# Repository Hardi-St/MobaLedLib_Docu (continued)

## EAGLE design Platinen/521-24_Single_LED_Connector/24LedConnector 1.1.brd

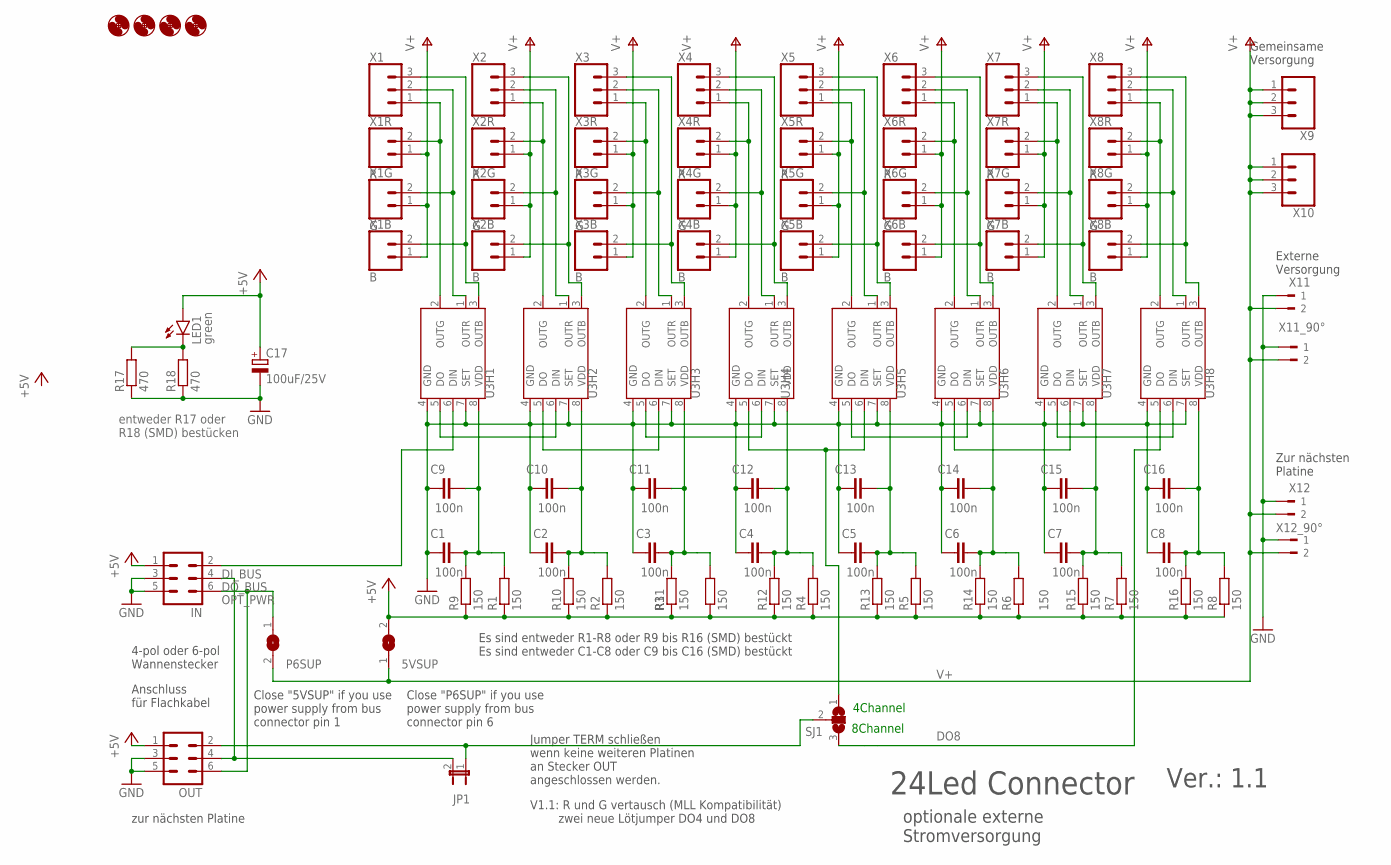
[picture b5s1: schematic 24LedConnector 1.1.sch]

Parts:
5VSUP: SJ
C1, C2, C3, C4, C5, C6, C7, C8: 100n; C025-024X044
C9, C10, C11, C12, C13, C14, C15, C16: 100n; C0805
C17: 100uF/25V; E3,5-8
H1, H2, H3, H4: MOUNT-HOLE2.0; 2,0
IN: ML6
JP1: JP1E; JP1
LED1: green; LED3MM
OUT: ML6
P6SUP: SJ
R1, R2, R3, R4, R5, R6, R7, R8: 150; 0204V
R9, R10, R11, R12, R13, R14, R15, R16: 150; M0805
R17: 470; M0805
R18: 470; 0204V
SJ1: SJ2W; SJ_2
U3H1, U3H2, U3H3, U3H4, U3H5, U3H6, U3H7, U3H8: WS2811; SOP8
X1, X2, X3, X4, X5, X6, X7, X8, X9, X10: CONN_03SCREW-NS; SCREWTERMINAL-3.5MM-3-NS
X1B, X2B, X3B, X4B, X5B, X6B, X7B, X8B: B; 1X02
X1G, X2G, X3G, X4G, X5G, X6G, X7G, X8G: G; 1X02
X1R, X2R, X3R, X4R, X5R, X6R, X7R, X8R: R; 1X02
X11, X12: 180-2
X11_90°, X12_90°: 90-2

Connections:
+5V: 5VSUP.2, C17.+, IN.1, LED1.A, OUT.1, R1.1, R2.1, R3.1, R4.1, R5.1, R6.1, R7.1, R8.1, R9.1, R10.1, R11.1, R12.1, R13.1, R14.1, R15.1, R16.1
B1: U3H1.3 (OUTB), X1.3, X1B.2
B2: U3H2.3 (OUTB), X2.3, X2B.2
B3: U3H3.3 (OUTB), X3.3, X3B.2
B4: U3H4.3 (OUTB), X4.3, X4B.2
B5: U3H5.3 (OUTB), X5.3, X5B.2
B6: U3H6.3 (OUTB), X6.3, X6B.2
B7: U3H7.3 (OUTB), X7.3, X7B.2
B8: U3H8.3 (OUTB), X8.3, X8B.2
DI_BUS: IN.2, U3H1.6 (DIN)
DO1DI2: U3H1.5 (DO), U3H2.6 (DIN)
DO2DI3: U3H2.5 (DO), U3H3.6 (DIN)
DO3DI4: U3H3.5 (DO), U3H4.6 (DIN)
DO4DI5: SJ1.1, U3H4.5 (DO), U3H5.6 (DIN)
DO5DI6: U3H5.5 (DO), U3H6.6 (DIN)
DO6DI7: U3H6.5 (DO), U3H7.6 (DIN)
DO7DI8: U3H7.5 (DO), U3H8.6 (DIN)
DO8: SJ1.3, U3H8.5 (DO)
DO_BUS: IN.4, JP1.2, OUT.4
DO_MODULE: JP1.1, OUT.2, SJ1.2
G1: U3H1.1 (OUTR), X1.2, X1G.2
G2: U3H2.1 (OUTR), X2.2, X2G.2
G3: U3H3.1 (OUTR), X3.2, X3G.2
G4: U3H4.1 (OUTR), X4.2, X4G.2
G5: U3H5.1 (OUTR), X5.2, X5G.2
G6: U3H6.1 (OUTR), X6.2, X6G.2
G7: U3H7.1 (OUTR), X7.2, X7G.2
G8: U3H8.1 (OUTR), X8.2, X8G.2
GND: C1.1, C2.1, C3.1, C4.1, C5.1, C6.1, C7.1, C8.1, C9.1, C10.1, C11.1, C12.1, C13.1, C14.1, C15.1, C16.1, C17.-, IN.3, IN.5, OUT.3, OUT.5, R17.1, R18.1, U3H1.4 (GND), U3H1.7 (SET), U3H2.4 (GND), U3H2.7 (SET), U3H3.4 (GND), U3H3.7 (SET), U3H4.4 (GND), U3H4.7 (SET), U3H5.4 (GND), U3H5.7 (SET), U3H6.4 (GND), U3H6.7 (SET), U3H7.4 (GND), U3H7.7 (SET), U3H8.4 (GND), U3H8.7 (SET), X11.1, X11_90°.1, X12.1, X12_90°.1
OPT_PWR: IN.6, OUT.6, P6SUP.1
POWERLED: LED1.K (C), R17.2, R18.2
R1: U3H1.2 (OUTG), X1.1, X1R.2
R2: U3H2.2 (OUTG), X2.1, X2R.2
R3: U3H3.2 (OUTG), X3.1, X3R.2
R4: U3H4.2 (OUTG), X4.1, X4R.2
R5: U3H5.2 (OUTG), X5.1, X5R.2
R6: U3H6.2 (OUTG), X6.1, X6R.2
R7: U3H7.2 (OUTG), X7.1, X7R.2
R8: U3H8.2 (OUTG), X8.1, X8R.2
V+: 5VSUP.1, P6SUP.2, X1B.1, X1G.1, X1R.1, X2B.1, X2G.1, X2R.1, X3B.1, X3G.1, X3R.1, X4B.1, X4G.1, X4R.1, X5B.1, X5G.1, X5R.1, X6B.1, X6G.1, X6R.1, X7B.1, X7G.1, X7R.1, X8B.1, X8G.1, X8R.1, X9.1, X9.2, X9.3, X10.1, X10.2, X10.3, X11.2, X11_90°.2, X12.2, X12_90°.2
VDD'1: C1.2, C9.2, R1.2, R9.2, U3H1.8 (VDD)
VDD'2: C2.2, C10.2, R2.2, R10.2, U3H2.8 (VDD)
VDD'3: C3.2, C11.2, R3.2, R11.2, U3H3.8 (VDD)
VDD'4: C4.2, C12.2, R4.2, R12.2, U3H4.8 (VDD)
VDD'5: C5.2, C13.2, R5.2, R13.2, U3H5.8 (VDD)
VDD'6: C6.2, C14.2, R6.2, R14.2, U3H6.8 (VDD)
VDD'7: C7.2, C15.2, R7.2, R15.2, U3H7.8 (VDD)
VDD'8: C8.2, C16.2, R8.2, R16.2, U3H8.8 (VDD)

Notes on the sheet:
Anschluss für Flachkabel
4-pol oder 6-pol Wannenstecker
Close "P6SUP" if you use power supply from bus connector pin 6
zur nächsten Platine
Gemeinsame Versorgung
24Led Connector
optionale externe Stromversorgung
Ver.: 1.1
Jumper TERM schließen wenn keine weiteren Platinen an Stecker OUT angeschlossen werden.
Zur nächsten Platine
Close "5VSUP" if you use power supply from bus connector pin 1
Externe Versorgung
Es sind entweder R1-R8 oder R9 bis R16 (SMD) bestückt Es sind entweder C1-C8 oder C9 bis C16 (SMD) bestückt
entweder R17 oder R18 (SMD) bestücken
V1.1: R und G vertausch (MLL Kompatibilität) zwei neue Lötjumper DO4 und DO8
4Channel
8Channel

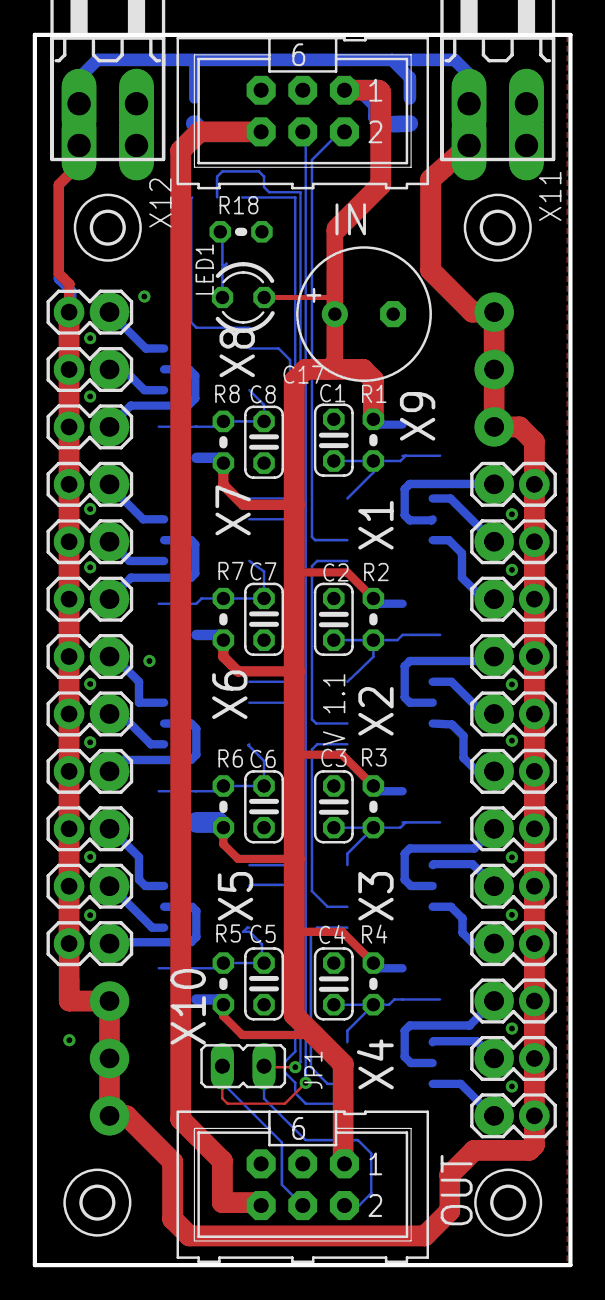
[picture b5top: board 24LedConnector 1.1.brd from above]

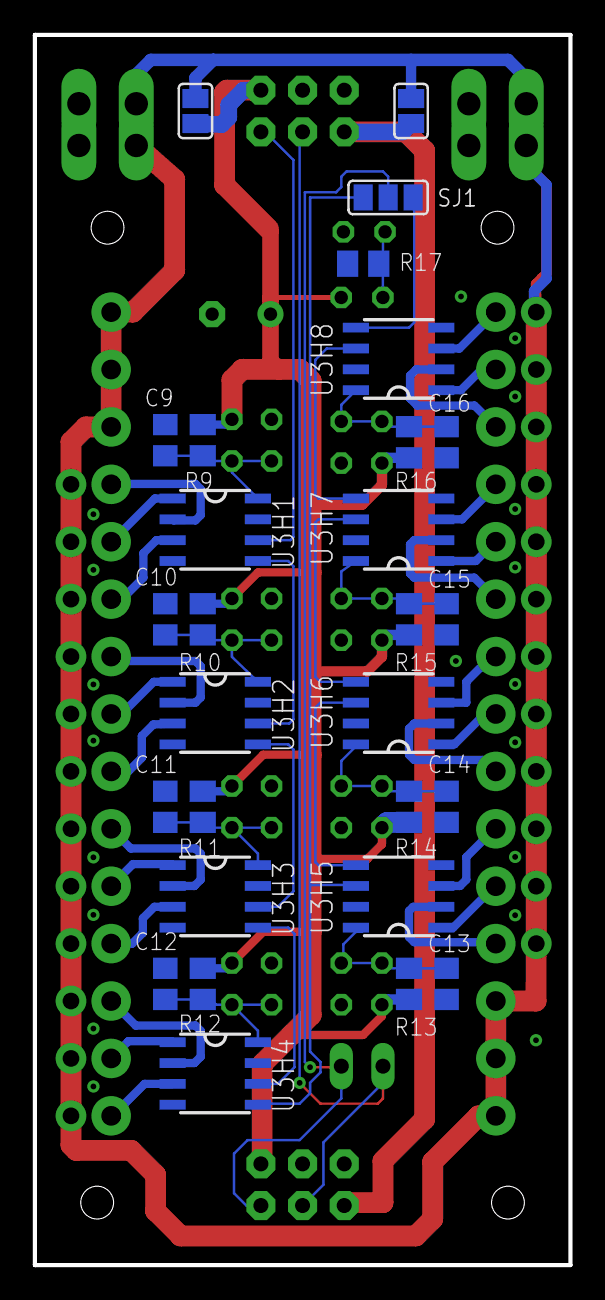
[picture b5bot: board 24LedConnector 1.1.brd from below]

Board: 2 copper layers, 32.7 x 75.0 mm, 92 parts (28 on the bottom side), 48 nets.

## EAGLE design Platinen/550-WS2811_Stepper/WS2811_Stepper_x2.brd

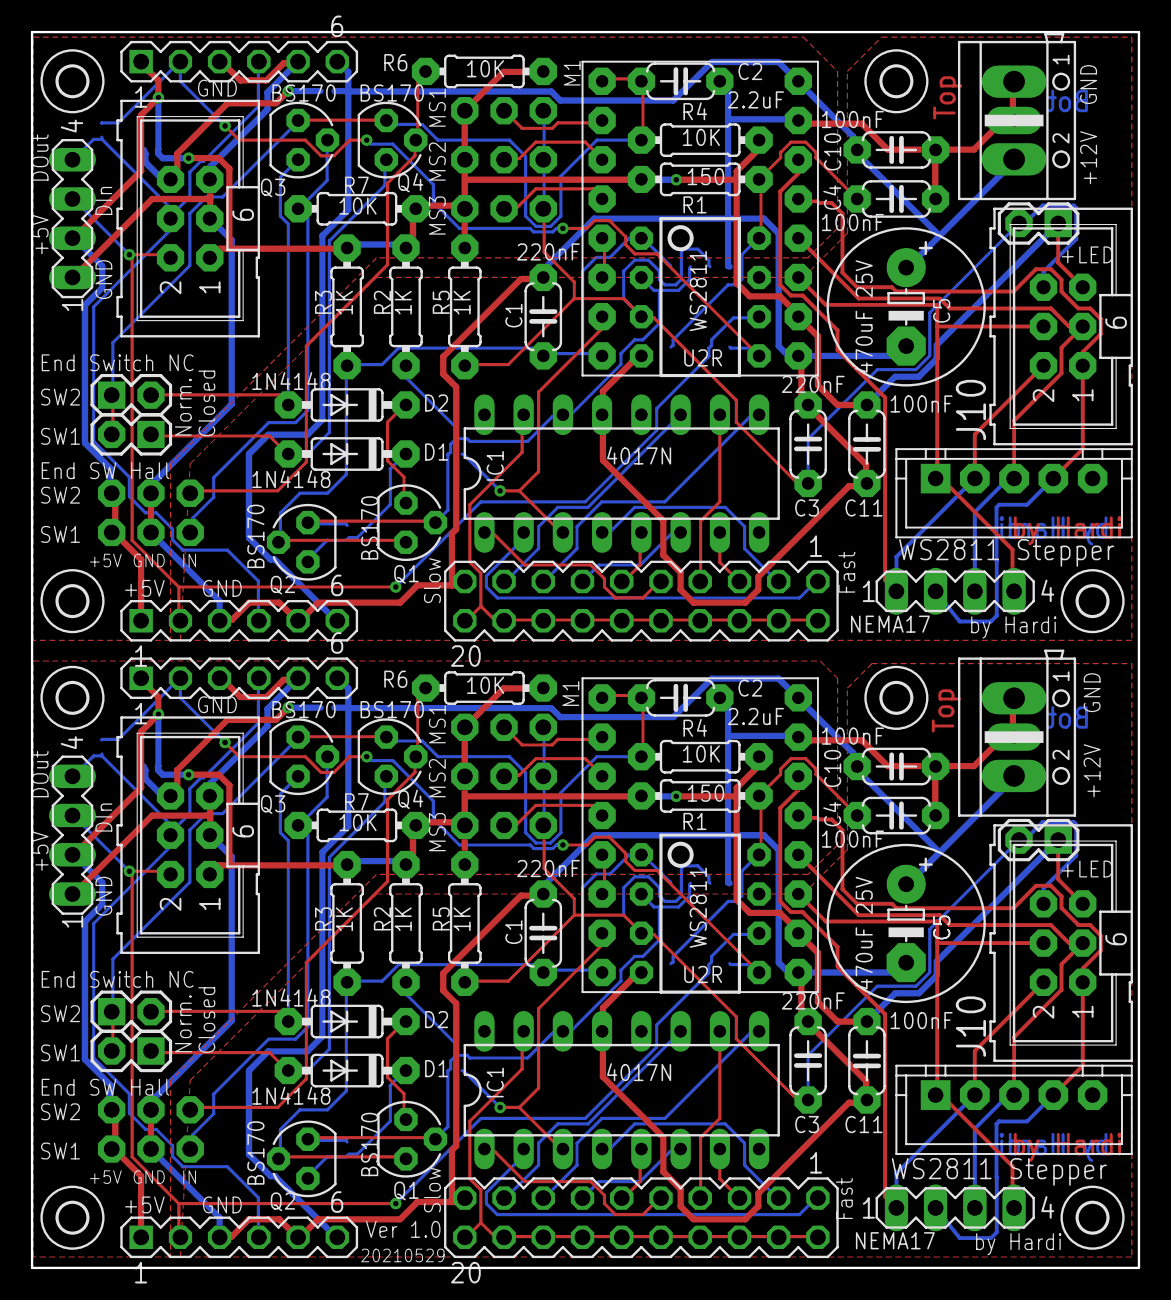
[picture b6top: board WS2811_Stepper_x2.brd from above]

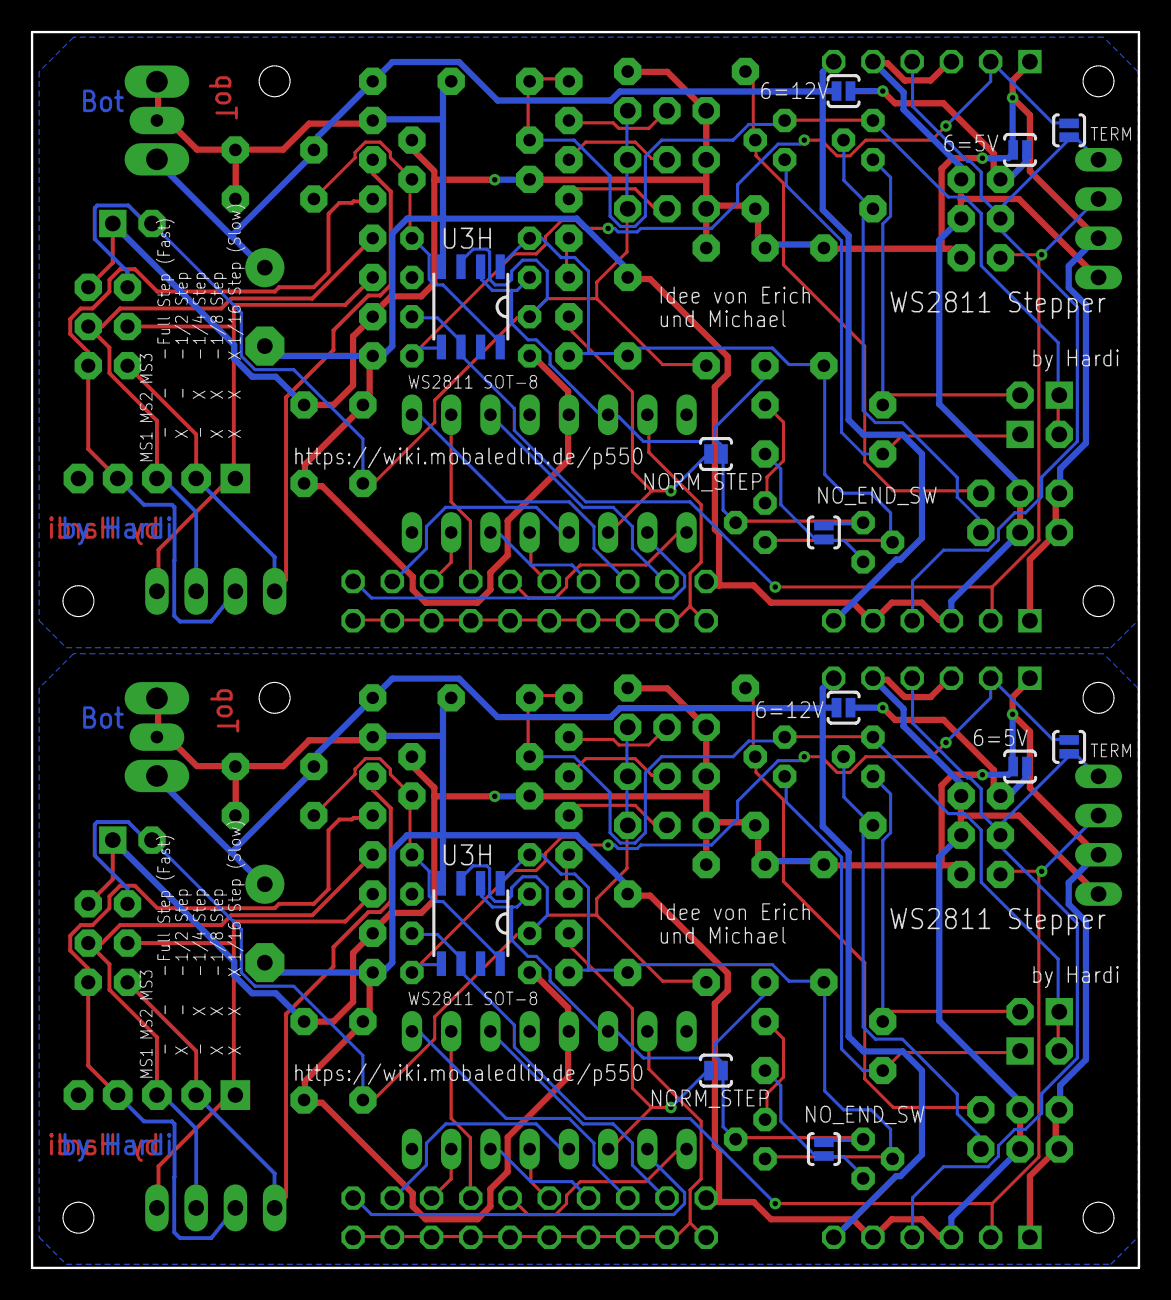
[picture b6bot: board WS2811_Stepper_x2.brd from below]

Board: 2 copper layers, 71.7 x 80.0 mm, 100 parts (12 on the bottom side), 74 nets.

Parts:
6=5V, 6=5V1, 6=12V, 6=12V1: SOLDERJUMPERNO; SJ_2S-NO
C1, C3, C6, C12: 220nF; C050-024X044
C2, C9: 2.2uF; C050-024X044
C4, C7, C8, C10, C11, C14: 100nF; C050-024X044
C5, C13: 470uF 25V; E5-10,5
CON1, CON8: End SW1; 1X02
CON2, CON9: End SW2; 1X02
CON3, CON11: End SW1H; 1X03-CLEANBIG
CON4, CON10: STEPPER_CON
CON5, CON12: End SW2H; 1X03-CLEANBIG
CON6, CON13: NEMA17; MA04-1
CON7, CON14: LED; 1X02
D1, D2, D3, D4: 1N4148; DO35-7
H1, H2, H3, H4, H5, H6, H7, H8: MOUNT-HOLE2.0; 2,0
IC1, IC2: 4017N; DIL16
IN, IN1: ML6
J1, J10: ML6
JP1, JP4: MS1; 1X03-CLEANBIG
JP2, JP5: MS2; 1X03-CLEANBIG
JP3, JP6: MS3; 1X03-CLEANBIG
M1, M2: BOARD_A4988
NORM_STEP, NORM_STEP1: SOLDERJUMPERNO; SJ_2S-NO
NO_END_SW, NO_END_SW1: SOLDERJUMPERNO; SJ_2S-NO
Q1, Q2, Q3, Q4, Q5, Q6, Q7, Q8: BS170; SOT54E
R1, R8: 150; RCL_0204/7
R2, R3, R5, R9, R10, R12: 1K; RCL_0204/7
R4, R6, R7, R11, R13, R14: 10K; RCL_0204/7
SV1, SV3, SV5, SV6: MA06-1
SV2, SV7: MA04-1
SV4, SV8: MA10-2
TERM, TERM1: SOLDERJUMPERNO; SJ_2S-NO
U2R, U2R1: WS2811; S3PO_MODUL_WS2811_SOUND_MP3-TF-16P_WS2811_AND_ATTINY_WS2811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
U3H, U3H1: WS2811 SOT-8; SOP8
X1, X2: AK500/2+M

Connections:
+5V: 6=5V.2, C11.1, CON3.1, CON5.1, CON7.1, IN.1, J10.5, JP1.1, JP2.1, JP3.1, M1.+5V, R1.1, R2.2, R3.2, R4.2, R5.2, R6.2, R7.2, SV1.1, SV2.2, SV3.1
+5V1: 6=5V1.2, C8.1, CON11.1, CON12.1, CON14.1, IN1.1, J1.5, JP4.1, JP5.1, JP6.1, M2.+5V, R8.1, R9.2, R10.2, R11.2, R12.2, R13.2, R14.2, SV5.1, SV6.1, SV7.2
DIR: C1.1, M1.DIR, Q1.S, Q2.G, R3.1, U2R.1, U3H.1
DIR1: C6.1, M2.DIR, Q5.S, Q6.G, R10.1, U2R1.1, U3H1.1
GND: C1.2, C2.2, C3.2, C4.2, C5.-, C10.2, C11.2, CON3.2, CON5.2, IC1.13, IN.3, IN.5, M1.GND, M1.GNDMOT, SV1.3, SV1.5, SV2.1, SV3.3, SV3.5, SV4.19, U2R.4, U3H.4, X1.1, X1.M
GND1: C6.2, C7.2, C8.2, C9.2, C12.2, C13.-, C14.2, CON11.2, CON12.2, IC2.13, IN1.3, IN1.5, M2.GND, M2.GNDMOT, SV5.3, SV5.5, SV6.3, SV6.5, SV7.1, SV8.19, U2R1.4, U3H1.4, X2.1, X2.M
LED: C3.1, CON7.2, J10.6, JP1.3, JP2.3, JP3.3, R5.1, U2R.3, U3H.3
LED1: C12.1, CON14.2, J1.6, JP4.3, JP5.3, JP6.3, R12.1, U2R1.3, U3H1.3
unnamed: M1.RESET, M1.SLEEP
unnamed: IN.2, SV1.2, SV2.3, U2R.6, U3H.6
unnamed: SV3.2, TERM.2, U2R.5, U3H.5
unnamed: IN.4, SV1.4, SV2.4, SV3.4, TERM.1
unnamed: C4.1, R1.2, U2R.8, U3H.8
unnamed: C2.1, CON1.1, CON2.2, M1.ENABLE, Q3.D, Q4.D, R4.1
unnamed: 6=12V.1, C5.+, C10.1, M1.VMOT, SV1.6, SV3.6, X1.2
unnamed: CON2.1, D1.A, Q4.S
unnamed: CON1.2, D2.A, Q3.S
unnamed: CON5.3, Q4.G, R6.1
unnamed: D2.C, Q1.D
unnamed: JP6.2, M2.MS3
unnamed: D1.C, NO_END_SW.1, Q2.D
unnamed: JP2.2, M1.MS2
unnamed: 6=5V.1, 6=12V.2, IN.6
unnamed: CON3.3, Q3.G, R7.1
unnamed: JP5.2, M2.MS2
unnamed: IC1.2, SV4.1
unnamed: IC1.4, SV4.3
unnamed: IC1.7, SV4.5
unnamed: IC1.10, SV4.7
unnamed: JP1.2, M1.MS1
unnamed: IC1.1, SV4.9
unnamed: IC1.5, SV4.11
unnamed: IC1.6, SV4.13
unnamed: IC1.9, SV4.15
unnamed: JP3.2, M1.MS3
unnamed: IC1.11, SV4.17
unnamed: IC1.15, SV4.2, SV4.4, SV4.6, SV4.8, SV4.10, SV4.12, SV4.14, SV4.16, SV4.18, SV4.20
unnamed: JP4.2, M2.MS1
unnamed: CON4.2, CON6.1, J10.2, M1.M2AB
unnamed: CON10.2, CON13.1, J1.2, M2.M2AB
unnamed: IC1.3, M1.STEP, NORM_STEP.2
unnamed: CON10.4, CON13.2, J1.1, M2.M2A
unnamed: CON4.1, CON6.4, J10.4, M1.M1B
unnamed: CON10.3, CON13.3, J1.3, M2.M1A
unnamed: CON10.1, CON13.4, J1.4, M2.M1B
unnamed: M2.RESET, M2.SLEEP
unnamed: IN1.2, SV5.2, SV7.3, U2R1.6, U3H1.6
unnamed: CON4.4, CON6.2, J10.1, M1.M2A
unnamed: CON4.3, CON6.3, J10.3, M1.M1A
unnamed: SV6.2, TERM1.2, U2R1.5, U3H1.5
unnamed: IN1.4, SV5.4, SV6.4, SV7.4, TERM1.1
unnamed: C14.1, R8.2, U2R1.8, U3H1.8
unnamed: 6=12V1.1, C7.1, C13.+, M2.VMOT, SV5.6, SV6.6, X2.2
unnamed: C9.1, CON8.1, CON9.2, M2.ENABLE, Q7.D, Q8.D, R11.1
unnamed: CON9.1, D3.A, Q8.S
unnamed: CON8.2, D4.A, Q7.S
unnamed: D4.C, Q5.D
unnamed: D3.C, NO_END_SW1.1, Q6.D
unnamed: CON11.3, Q7.G, R14.1
unnamed: CON12.3, Q8.G, R13.1
unnamed: IC2.4, SV8.3
unnamed: IC2.7, SV8.5
unnamed: IC2.10, SV8.7
unnamed: IC2.1, SV8.9
unnamed: IC2.5, SV8.11
unnamed: IC2.6, SV8.13
unnamed: IC2.9, SV8.15
unnamed: IC2.11, SV8.17
unnamed: IC2.15, SV8.2, SV8.4, SV8.6, SV8.8, SV8.10, SV8.12, SV8.14, SV8.16, SV8.18, SV8.20
unnamed: IC2.3, M2.STEP, NORM_STEP1.2
unnamed: IC2.2, SV8.1
unnamed: 6=5V1.1, 6=12V1.2, IN1.6
STEP: IC1.14, NORM_STEP.1, NO_END_SW.2, Q1.G, Q2.S, R2.1, U2R.2, U3H.2
STEP1: IC2.14, NORM_STEP1.1, NO_END_SW1.2, Q5.G, Q6.S, R9.1, U2R1.2, U3H1.2

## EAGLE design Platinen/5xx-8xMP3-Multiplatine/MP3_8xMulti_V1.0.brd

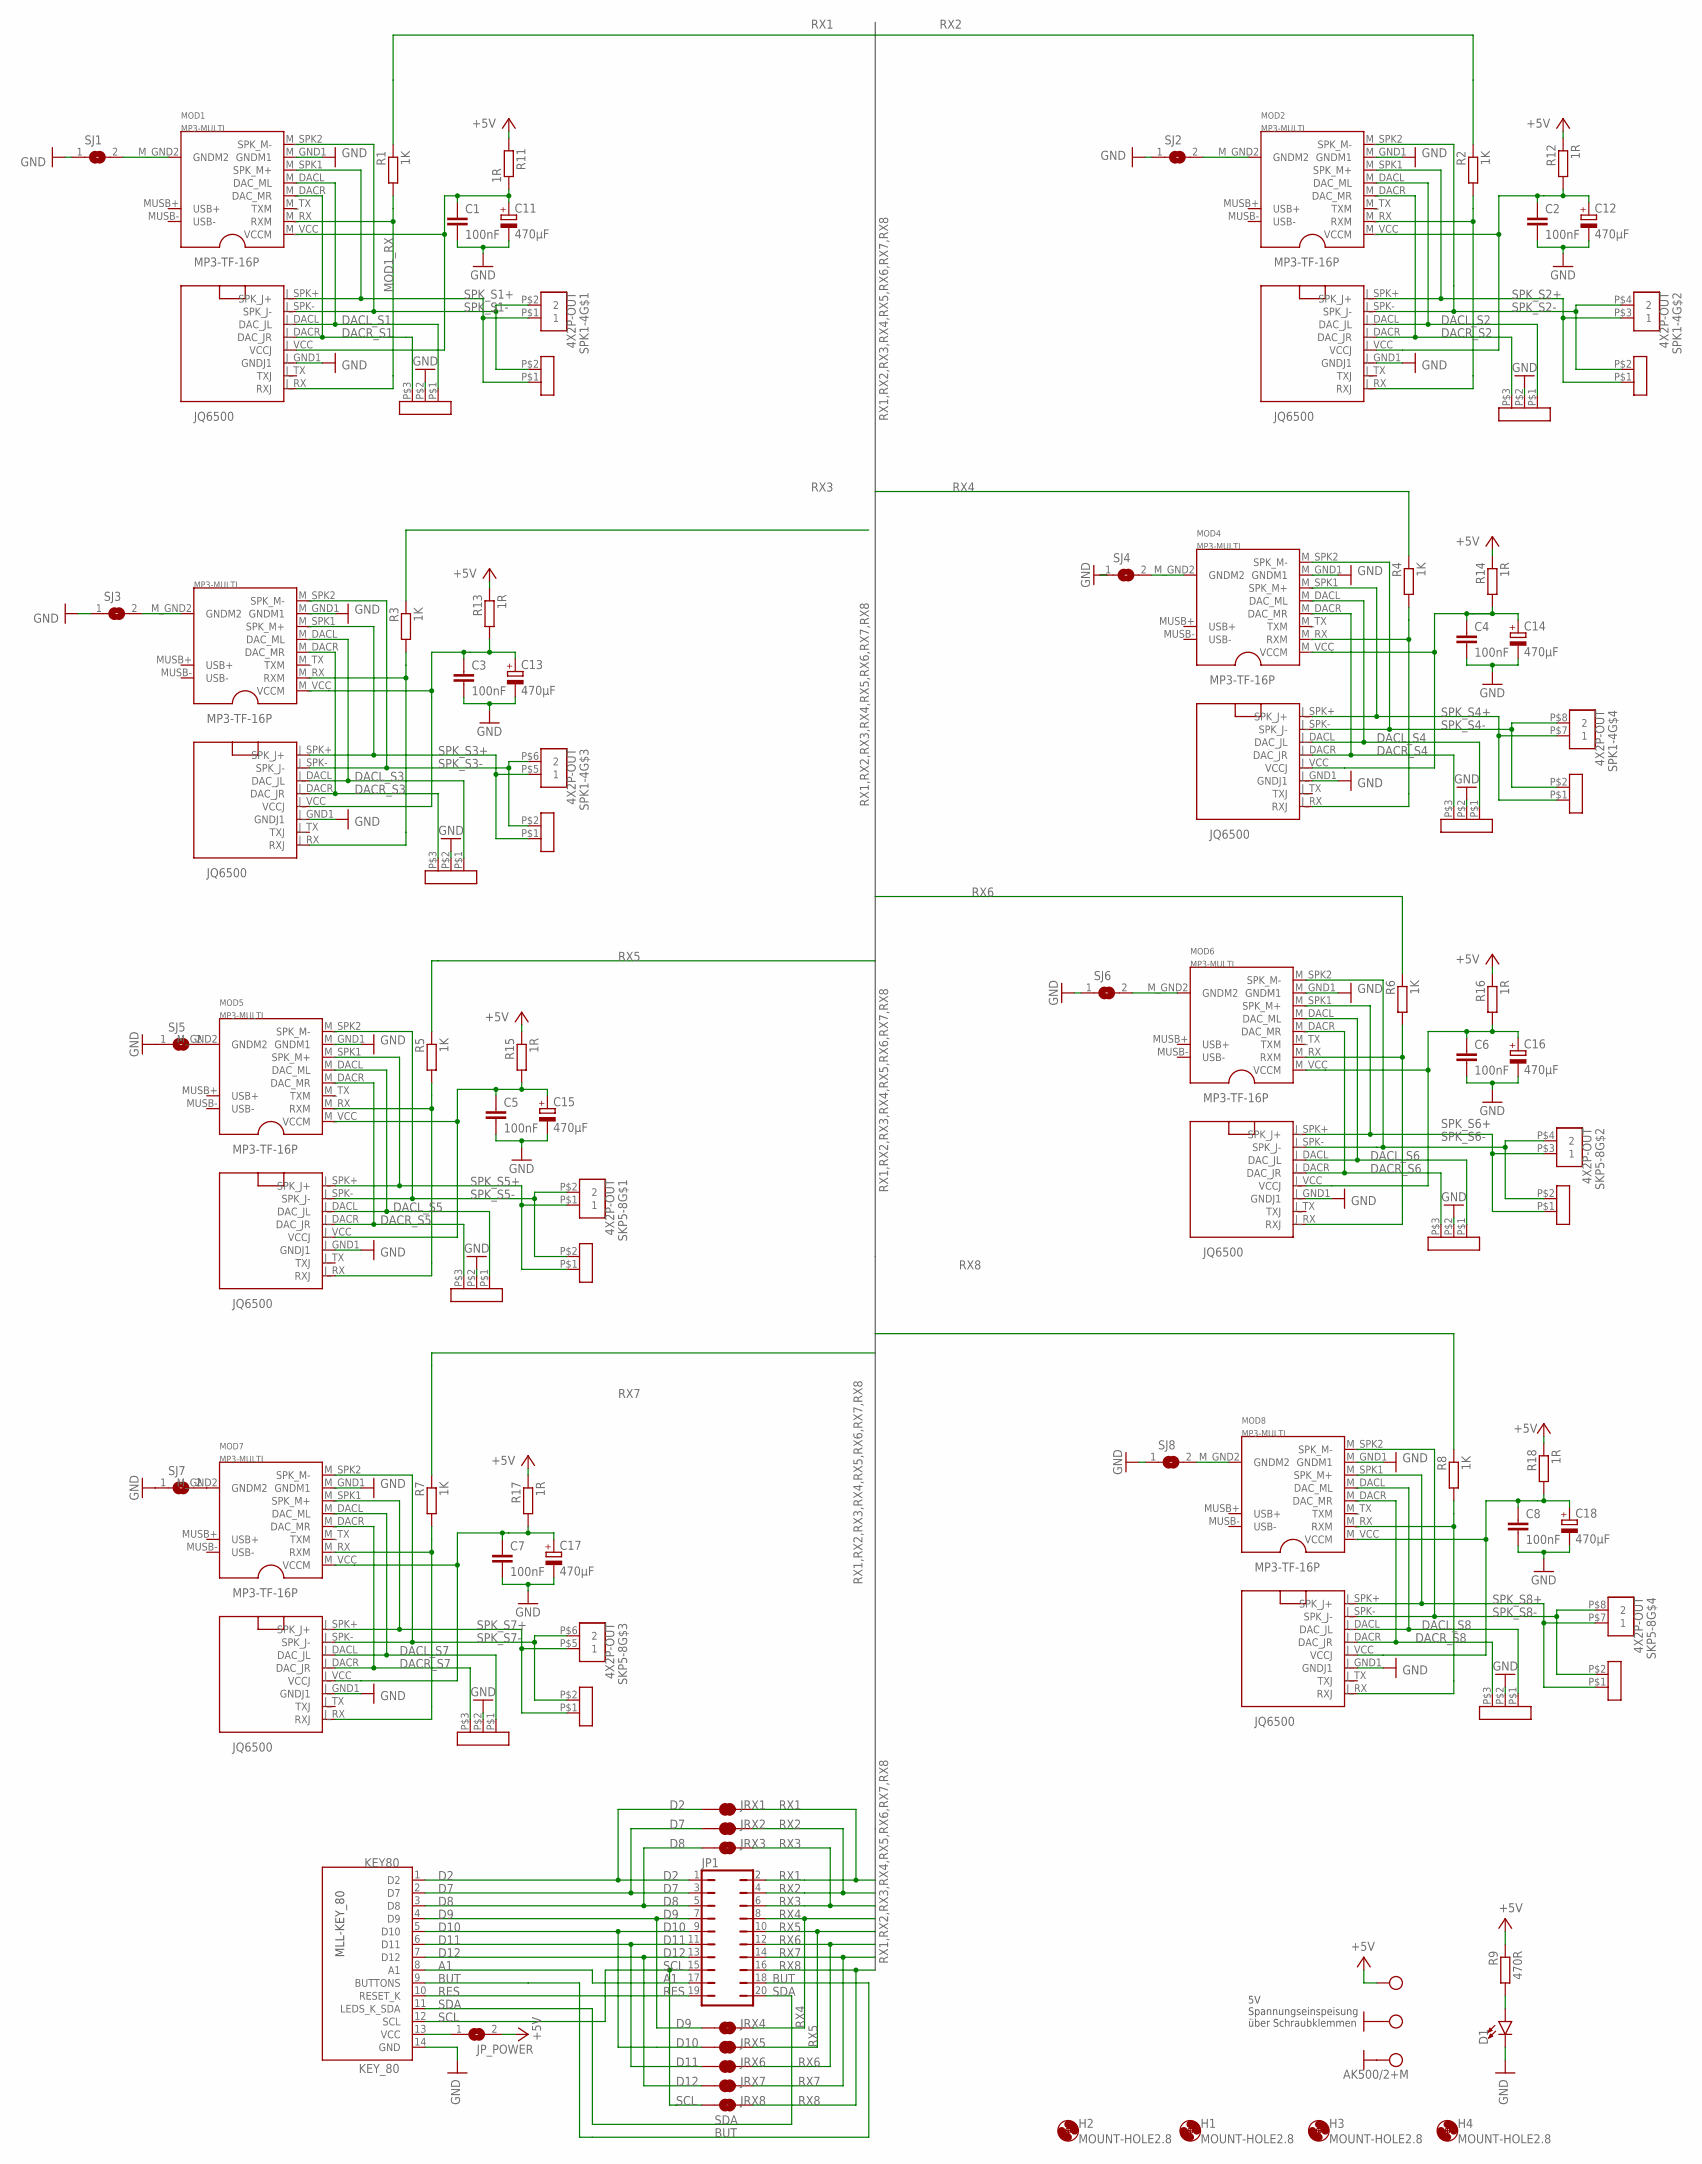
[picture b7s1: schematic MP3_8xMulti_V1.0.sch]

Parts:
C1, C2, C3, C4, C5, C6, C7, C8: 100nF; C025-025X050
C11, C12, C13, C14, C15, C16, C17, C18: 470µF; E5-8,5
D1: LED3MM; LED_3MM
DAC1, DAC2, DAC3, DAC4, DAC5, DAC6, DAC7, DAC8: 3XRM254
H1, H2, H3, H4: MOUNT-HOLE2.8; 2,8
JP1: JP10Q
JP_POWER: SJ
JRX1, JRX2, JRX3, JRX4, JRX5, JRX6, JRX7, JRX8: JUMPER-SMT_2_NC_TRACE_NO-SILK; SMT-JUMPER_2_NC_TRACE_NO-SILK
KEY80: KEY_80; IDC14
MOD1, MOD2, MOD3, MOD4, MOD5, MOD6, MOD7, MOD8: MP3-MULTI; MP3-TF16P_JQ6500
R1, R2, R3, R4, R5, R6, R7, R8: 1K; 0207/7
R9: 470R; 0207/7
R11, R12, R13, R14, R15, R16, R17, R18: 1R; 0207/7
SJ1, SJ2, SJ3, SJ4, SJ5, SJ6, SJ7, SJ8: SJ
SKP5-8: 4X2P-OUT; DG308
SPK1, SPK2, SPK3, SPK4, SPK5, SPK6, SPK7, SPK8: 2XRM254
SPK1-4: 4X2P-OUT; DG308
X1: AK500/2+M

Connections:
+5V: JP_POWER.2, R9.1, R11.2, R12.1, R13.1, R14.1, R15.1, R16.1, R17.1, R18.1, X1.2
A1: JP1.17, KEY80.8 (A1)
BUT: JP1.18, KEY80.9 (BUTTONS)
D2: JP1.1, JRX1.1, KEY80.1 (D2)
D7: JP1.3, JRX2.1, KEY80.2 (D7)
D8: JP1.5, JRX3.1, KEY80.3 (D8)
D9: JP1.7, JRX4.1, KEY80.4 (D9)
D10: JP1.9, JRX5.1, KEY80.5 (D10)
D11: JP1.11, JRX6.1, KEY80.6 (D11)
D12: JP1.13, JRX7.1, KEY80.7 (D12)
DACL_S1: DAC1.P$1, MOD1.J_DACL (DAC_JL), MOD1.M_DACL (DAC_ML)
DACL_S2: DAC2.P$1, MOD2.J_DACL (DAC_JL), MOD2.M_DACL (DAC_ML)
DACL_S3: DAC3.P$1, MOD3.J_DACL (DAC_JL), MOD3.M_DACL (DAC_ML)
DACL_S4: DAC4.P$1, MOD4.J_DACL (DAC_JL), MOD4.M_DACL (DAC_ML)
DACL_S5: DAC5.P$1, MOD5.J_DACL (DAC_JL), MOD5.M_DACL (DAC_ML)
DACL_S6: DAC6.P$1, MOD6.J_DACL (DAC_JL), MOD6.M_DACL (DAC_ML)
DACL_S7: DAC7.P$1, MOD7.J_DACL (DAC_JL), MOD7.M_DACL (DAC_ML)
DACL_S8: DAC8.P$1, MOD8.J_DACL (DAC_JL), MOD8.M_DACL (DAC_ML)
DACR_S1: DAC1.P$3, MOD1.J_DACR (DAC_JR), MOD1.M_DACR (DAC_MR)
DACR_S2: DAC2.P$3, MOD2.J_DACR (DAC_JR), MOD2.M_DACR (DAC_MR)
DACR_S3: DAC3.P$3, MOD3.J_DACR (DAC_JR), MOD3.M_DACR (DAC_MR)
DACR_S4: DAC4.P$3, MOD4.J_DACR (DAC_JR), MOD4.M_DACR (DAC_MR)
DACR_S5: DAC5.P$3, MOD5.J_DACR (DAC_JR), MOD5.M_DACR (DAC_MR)
DACR_S6: DAC6.P$3, MOD6.J_DACR (DAC_JR), MOD6.M_DACR (DAC_MR)
DACR_S7: DAC7.P$3, MOD7.J_DACR (DAC_JR), MOD7.M_DACR (DAC_MR)
DACR_S8: DAC8.P$3, MOD8.J_DACR (DAC_JR), MOD8.M_DACR (DAC_MR)
GND: C1.2, C2.2, C3.2, C4.2, C5.2, C6.2, C7.2, C8.2, C11.-, C12.-, C13.-, C14.-, C15.-, C16.-, C17.-, C18.-, D1.K (C), DAC1.P$2, DAC2.P$2, DAC3.P$2, DAC4.P$2, DAC5.P$2, DAC6.P$2, DAC7.P$2, DAC8.P$2, KEY80.14 (GND), MOD1.J_GND1 (GNDJ1), MOD1.M_GND1 (GNDM1), MOD2.J_GND1 (GNDJ1), MOD2.M_GND1 (GNDM1), MOD3.J_GND1 (GNDJ1), MOD3.M_GND1 (GNDM1), MOD4.J_GND1 (GNDJ1), MOD4.M_GND1 (GNDM1), MOD5.J_GND1 (GNDJ1), MOD5.M_GND1 (GNDM1), MOD6.J_GND1 (GNDJ1), MOD6.M_GND1 (GNDM1), MOD7.J_GND1 (GNDJ1), MOD7.M_GND1 (GNDM1), MOD8.J_GND1 (GNDJ1), MOD8.M_GND1 (GNDM1), SJ1.1, SJ2.1, SJ3.1, SJ4.1, SJ5.1, SJ6.1, SJ7.1, SJ8.1, X1.1, X1.M
LED1: D1.A, R9.2
MOD1_RX: MOD1.J_RX (RXJ), MOD1.M_RX (RXM), R1.2
MOD1_RX1: MOD2.J_RX (RXJ), MOD2.M_RX (RXM), R2.2
MOD1_RX2: MOD3.J_RX (RXJ), MOD3.M_RX (RXM), R3.2
MOD1_RX3: MOD4.J_RX (RXJ), MOD4.M_RX (RXM), R4.2
MOD1_RX4: MOD5.J_RX (RXJ), MOD5.M_RX (RXM), R5.2
MOD1_RX5: MOD6.J_RX (RXJ), MOD6.M_RX (RXM), R6.2
MOD1_RX6: MOD7.J_RX (RXJ), MOD7.M_RX (RXM), R7.2
MOD1_RX7: MOD8.J_RX (RXJ), MOD8.M_RX (RXM), R8.2
M_GND1: MOD1.M_GND2 (GNDM2), SJ1.2
M_GND2: MOD2.M_GND2 (GNDM2), SJ2.2
M_GND3: MOD3.M_GND2 (GNDM2), SJ3.2
M_GND4: MOD4.M_GND2 (GNDM2), SJ4.2
M_GND5: MOD5.M_GND2 (GNDM2), SJ5.2
M_GND6: MOD6.M_GND2 (GNDM2), SJ6.2
M_GND7: MOD7.M_GND2 (GNDM2), SJ7.2
M_GND8: MOD8.M_GND2 (GNDM2), SJ8.2
OPT-VCC: JP_POWER.1, KEY80.13 (VCC)
RES: JP1.19, KEY80.10 (RESET_K)
RX1: JP1.2, JRX1.2, R1.1
RX2: JP1.4, JRX2.2, R2.1
RX3: JP1.6, JRX3.2, R3.1
RX4: JP1.8, JRX4.2, R4.1
RX5: JP1.10, JRX5.2, R5.1
RX6: JP1.12, JRX6.2, R6.1
RX7: JP1.14, JRX7.2, R7.1
RX8: JP1.16, JRX8.2, R8.1
SCL: JP1.15, JRX8.1, KEY80.12 (SCL)
SDA: JP1.20, KEY80.11 (LEDS_K_SDA)
SOUND1_VCC: C1.1, C11.+, MOD1.J_VCC (VCCJ), MOD1.M_VCC (VCCM), R11.1
SOUND2_VCC: C2.1, C12.+, MOD2.J_VCC (VCCJ), MOD2.M_VCC (VCCM), R12.2
SOUND3_VCC: C3.1, C13.+, MOD3.J_VCC (VCCJ), MOD3.M_VCC (VCCM), R13.2
SOUND4_VCC: C4.1, C14.+, MOD4.J_VCC (VCCJ), MOD4.M_VCC (VCCM), R14.2
SOUND5_VCC: C5.1, C15.+, MOD5.J_VCC (VCCJ), MOD5.M_VCC (VCCM), R15.2
SOUND6_VCC: C6.1, C16.+, MOD6.J_VCC (VCCJ), MOD6.M_VCC (VCCM), R16.2
SOUND7_VCC: C7.1, C17.+, MOD7.J_VCC (VCCJ), MOD7.M_VCC (VCCM), R17.2
SOUND8_VCC: C8.1, C18.+, MOD8.J_VCC (VCCJ), MOD8.M_VCC (VCCM), R18.2
SPK_S1+: MOD1.J_SPK+ (SPK_J+), MOD1.M_SPK1 (SPK_M+), SPK1.P$1, SPK1-4.P$1 (1)
SPK_S1-: MOD1.J_SPK- (SPK_J-), MOD1.M_SPK2 (SPK_M-), SPK1.P$2, SPK1-4.P$2 (2)
SPK_S2+: MOD2.J_SPK+ (SPK_J+), MOD2.M_SPK1 (SPK_M+), SPK1-4.P$3 (1), SPK2.P$1
SPK_S2-: MOD2.J_SPK- (SPK_J-), MOD2.M_SPK2 (SPK_M-), SPK1-4.P$4 (2), SPK2.P$2
SPK_S3+: MOD3.J_SPK+ (SPK_J+), MOD3.M_SPK1 (SPK_M+), SPK1-4.P$5 (1), SPK3.P$1
SPK_S3-: MOD3.J_SPK- (SPK_J-), MOD3.M_SPK2 (SPK_M-), SPK1-4.P$6 (2), SPK3.P$2
SPK_S4+: MOD4.J_SPK+ (SPK_J+), MOD4.M_SPK1 (SPK_M+), SPK1-4.P$7 (1), SPK4.P$1
SPK_S4-: MOD4.J_SPK- (SPK_J-), MOD4.M_SPK2 (SPK_M-), SPK1-4.P$8 (2), SPK4.P$2
SPK_S5+: MOD5.J_SPK+ (SPK_J+), MOD5.M_SPK1 (SPK_M+), SKP5-8.P$1 (1), SPK5.P$1
SPK_S5-: MOD5.J_SPK- (SPK_J-), MOD5.M_SPK2 (SPK_M-), SKP5-8.P$2 (2), SPK5.P$2
SPK_S6+: MOD6.J_SPK+ (SPK_J+), MOD6.M_SPK1 (SPK_M+), SKP5-8.P$3 (1), SPK6.P$1
SPK_S6-: MOD6.J_SPK- (SPK_J-), MOD6.M_SPK2 (SPK_M-), SKP5-8.P$4 (2), SPK6.P$2
SPK_S7+: MOD7.J_SPK+ (SPK_J+), MOD7.M_SPK1 (SPK_M+), SKP5-8.P$5 (1), SPK7.P$1
SPK_S7-: MOD7.J_SPK- (SPK_J-), MOD7.M_SPK2 (SPK_M-), SKP5-8.P$6 (2), SPK7.P$2
SPK_S8+: MOD8.J_SPK+ (SPK_J+), MOD8.M_SPK1 (SPK_M+), SKP5-8.P$7 (1), SPK8.P$1
SPK_S8-: MOD8.J_SPK- (SPK_J-), MOD8.M_SPK2 (SPK_M-), SKP5-8.P$8 (2), SPK8.P$2

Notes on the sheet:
5V Spannungseinspeisung über Schraubklemmen

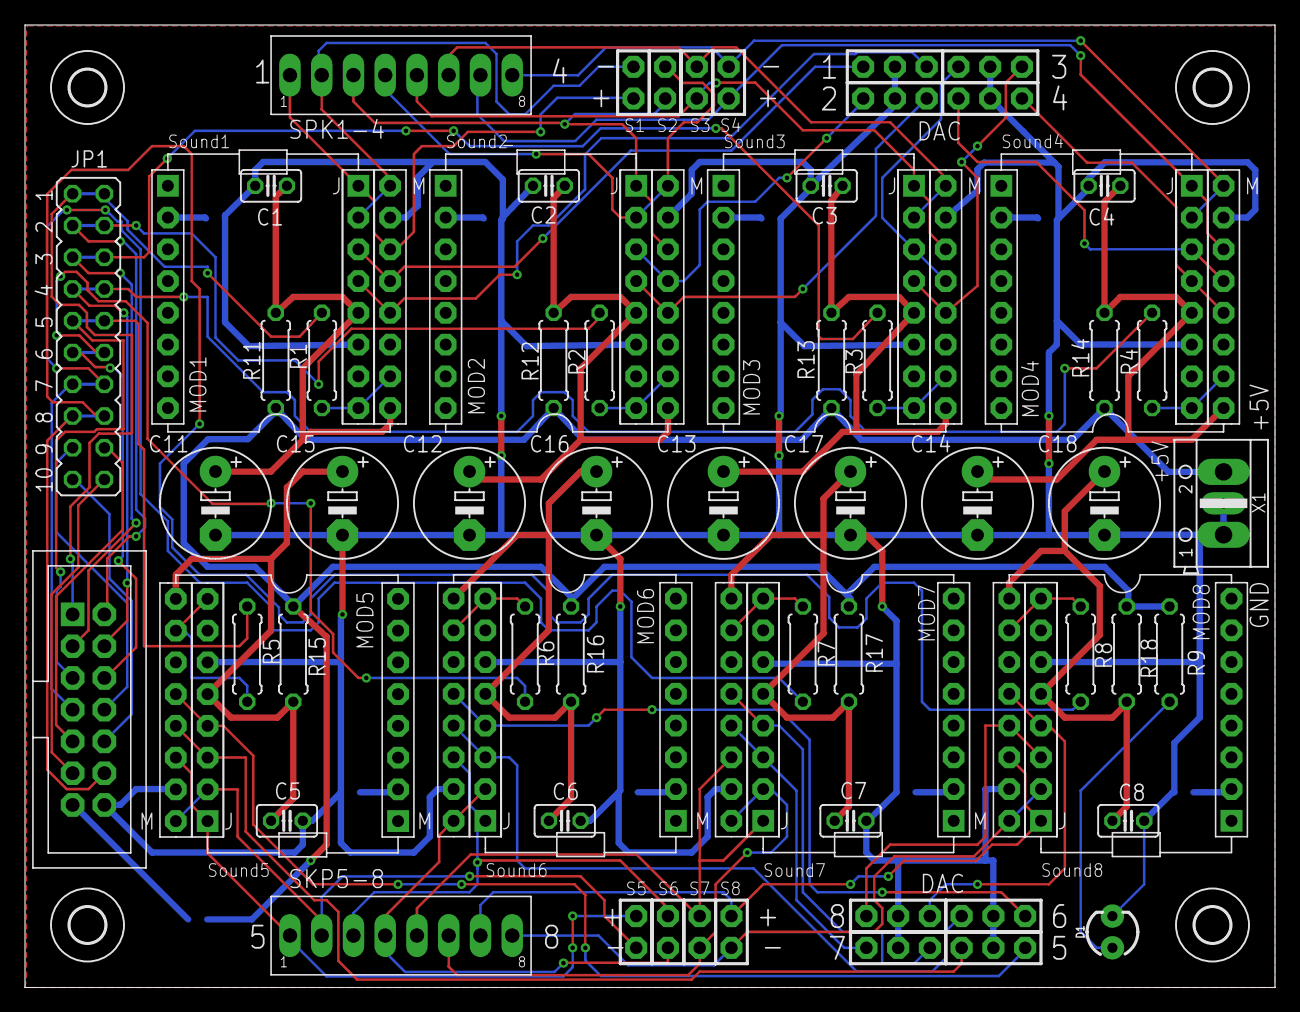
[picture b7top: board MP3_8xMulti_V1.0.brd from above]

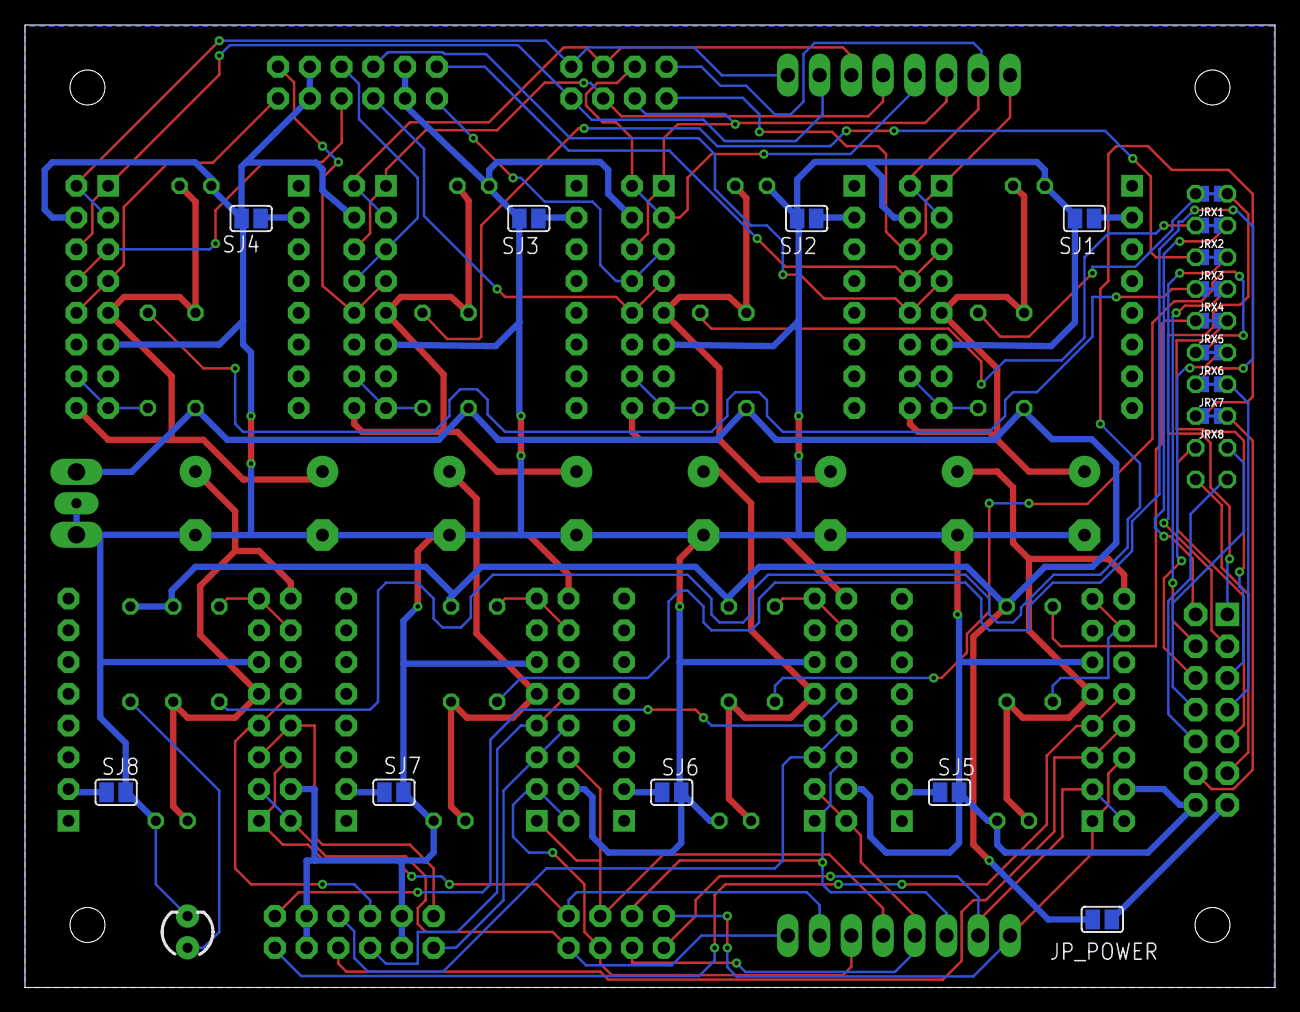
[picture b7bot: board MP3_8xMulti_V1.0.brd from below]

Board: 2 copper layers, 100.0 x 77.0 mm, 84 parts (17 on the bottom side), 80 nets.
